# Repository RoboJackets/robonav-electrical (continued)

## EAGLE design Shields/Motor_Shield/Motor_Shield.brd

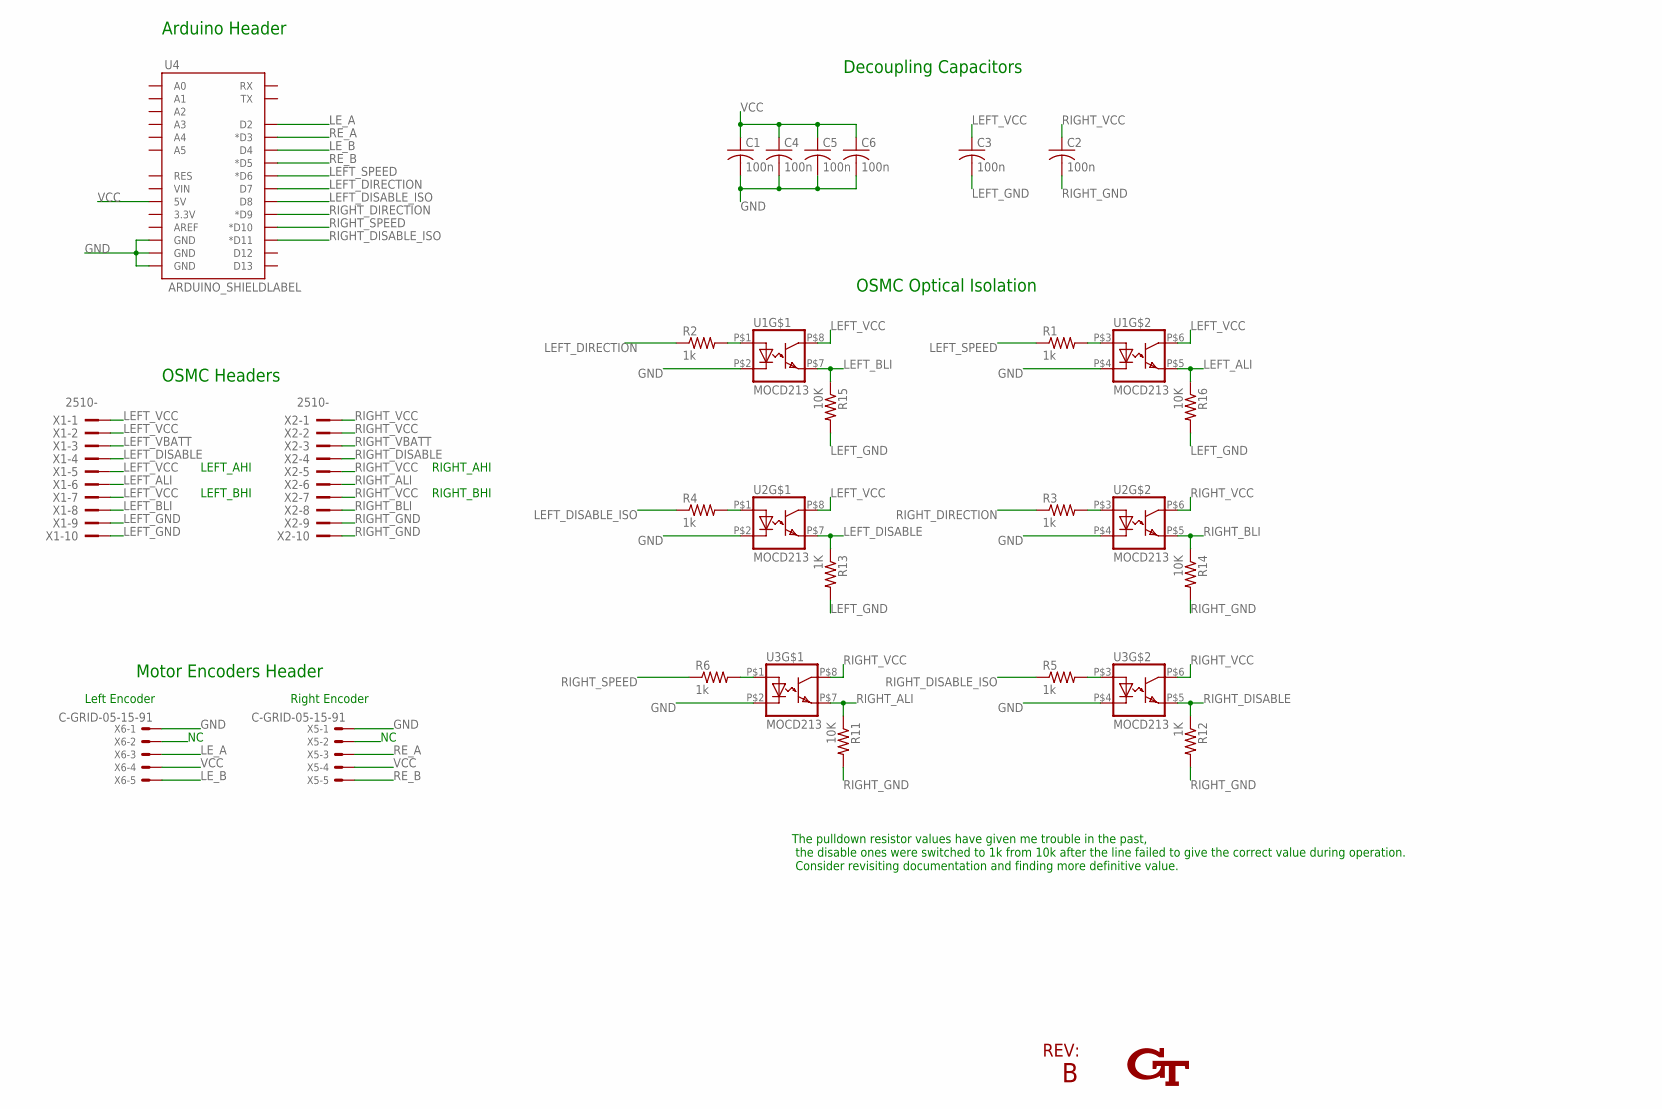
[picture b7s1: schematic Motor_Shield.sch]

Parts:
C1, C2, C3, C4, C5, C6: 100n; C0603
GT1: INTERLOCKING_GTSTOP_.5_INCH; GT_STOP_.5INCH
R1, R2, R3, R4, R5, R6: 1k; R0603
R11, R14, R15, R16: 10K; R0603
R12, R13: 1K; R0603
U1, U2, U3: MOCD213; SOIC-8
U4: ARDUINO_SHIELDLABEL; DUEMILANOVE_SHIELD
U$1: B; REV_BLOCK_14PT
X1, X2: 2510-; PAK100/2500-10
X5, X6: C-GRID-05-15-91; 15-91-05

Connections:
GND: C1.2, C4.2, C5.2, C6.2, U1.P$2 (C), U1.P$4 (C), U2.P$2 (C), U2.P$4 (C), U3.P$2 (C), U3.P$4 (C), U4.GND@0 (GND), U4.GND@1 (GND), U4.GND@2 (GND), X5.1, X6.1
LEFT_ALI: R16.1, U1.P$5 (EMIT), X1.6
LEFT_BLI: R15.1, U1.P$7 (EMIT), X1.8
LEFT_DIRECTION: R2.1, U4.D7
LEFT_DISABLE: R13.1, U2.P$7 (EMIT), X1.4
LEFT_DISABLE_ISO: R4.1, U4.D8
LEFT_GND: C3.2, R13.2, R15.2, R16.2, X1.9, X1.10
LEFT_SPEED: R1.1, U4.D6 (*D6)
LEFT_VBATT: X1.3
LEFT_VCC: C3.1, U1.P$6 (COL), U1.P$8 (COL), U2.P$8 (COL), X1.1, X1.2, X1.5, X1.7
LE_A: U4.D2, X6.3
LE_B: U4.D4, X6.5
unnamed: R2.2, U1.P$1 (A)
unnamed: R3.2, U2.P$3 (A)
unnamed: R6.2, U3.P$1 (A)
unnamed: R4.2, U2.P$1 (A)
unnamed: R1.2, U1.P$3 (A)
unnamed: R5.2, U3.P$3 (A)
RE_A: U4.D3 (*D3), X5.3
RE_B: U4.D5 (*D5), X5.5
RIGHT_ALI: R11.1, U3.P$7 (EMIT), X2.6
RIGHT_BLI: R14.1, U2.P$5 (EMIT), X2.8
RIGHT_DIRECTION: R3.1, U4.D9 (*D9)
RIGHT_DISABLE: R12.1, U3.P$5 (EMIT), X2.4
RIGHT_DISABLE_ISO: R5.1, U4.D11 (*D11)
RIGHT_GND: C2.2, R11.2, R12.2, R14.2, X2.9, X2.10
RIGHT_SPEED: R6.1, U4.D10 (*D10)
RIGHT_VBATT: X2.3
RIGHT_VCC: C2.1, U2.P$6 (COL), U3.P$6 (COL), U3.P$8 (COL), X2.1, X2.2, X2.5, X2.7
VCC: C1.1, C4.1, C5.1, C6.1, U4.5V, X5.4, X6.4

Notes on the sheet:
Motor Encoders Header
LEFT_AHI
LEFT_BHI
RIGHT_AHI
RIGHT_BHI
OSMC Headers
OSMC Optical Isolation
Decoupling Capacitors
Left Encoder
Right Encoder
Arduino Header
The pulldown resistor values have given me trouble in the past, the disable ones were switched to 1k from 10k after the line failed to give the correct value during operation. Consider revisiting documentation and finding more definitive value.

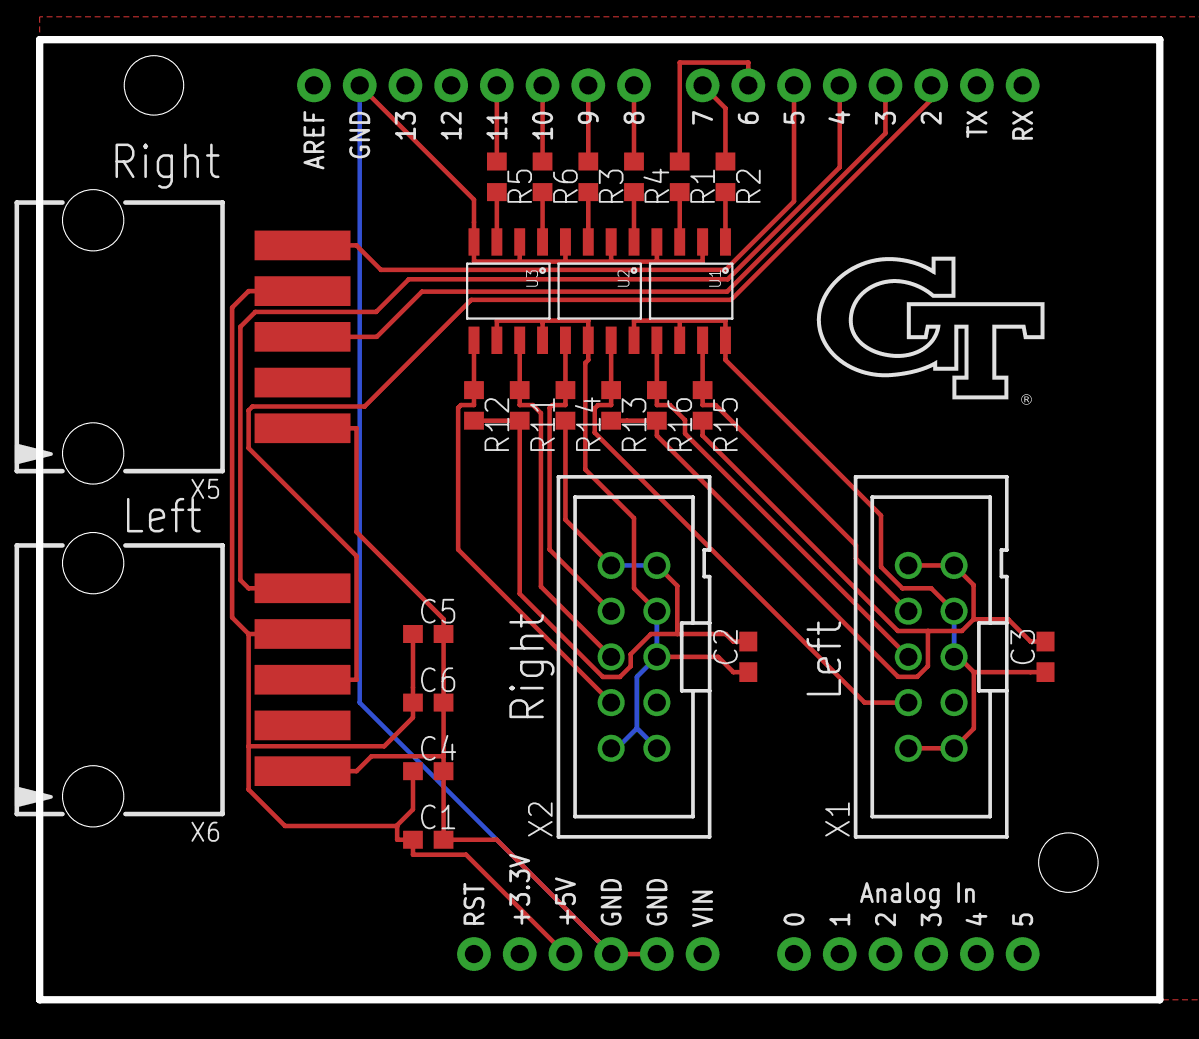
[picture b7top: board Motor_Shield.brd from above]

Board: 2 copper layers, 62.2 x 53.3 mm, 28 parts (1 on the bottom side), 28 nets.
